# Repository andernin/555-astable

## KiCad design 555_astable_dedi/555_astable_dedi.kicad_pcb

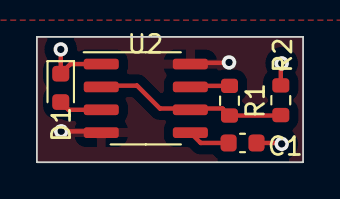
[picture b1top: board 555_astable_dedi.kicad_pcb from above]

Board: 2 copper layers, 14.8 x 7.0 mm, 5 parts (0 on the bottom side), 6 nets.

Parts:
C1: C; C_0603_1608Metric
D1: LED; LED_0603_1608Metric
R1, R2: R; R_0603_1608Metric
U2: NE555D; SOIC-8_3.9x4.9mm_P1.27mm

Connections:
/TR: R1.2, R2.1, U2.2 (TR), U2.6 (THR)
GND: C1.2, D1.1 (K), R2.2, U2.1 (GND)
unnamed: D1.2 (A), U2.3 (Q)
unnamed: C1.1, U2.5 (CV)
unnamed: R1.1, U2.7 (DIS)
VCC: U2.4 (R), U2.8 (VCC)

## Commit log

2024-09-22 555astable dedi
2024-09-22 README.md
